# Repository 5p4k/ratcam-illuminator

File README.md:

Ratcam Illuminator
==================

**Official repository: [https://git.mittelab.org/proj/ratcam-illuminator](https://git.mittelab.org/proj/ratcam-illuminator)**

> Ratcam allows you to control your RaspberryPi camera through a Telegram bot, and alerts you when movement is detected, by sending photos and videos.

This project includes schematics for the IR illuminator board.

Please refer to the wiki page:
  - [Ratcam wiki (IT)](https://wiki.mittelab.org/progetti/5p4k/ratcam)
  - [Ratcam wiki (EN)](https://wiki.mittelab.org/en/progetti/5p4k/ratcam)

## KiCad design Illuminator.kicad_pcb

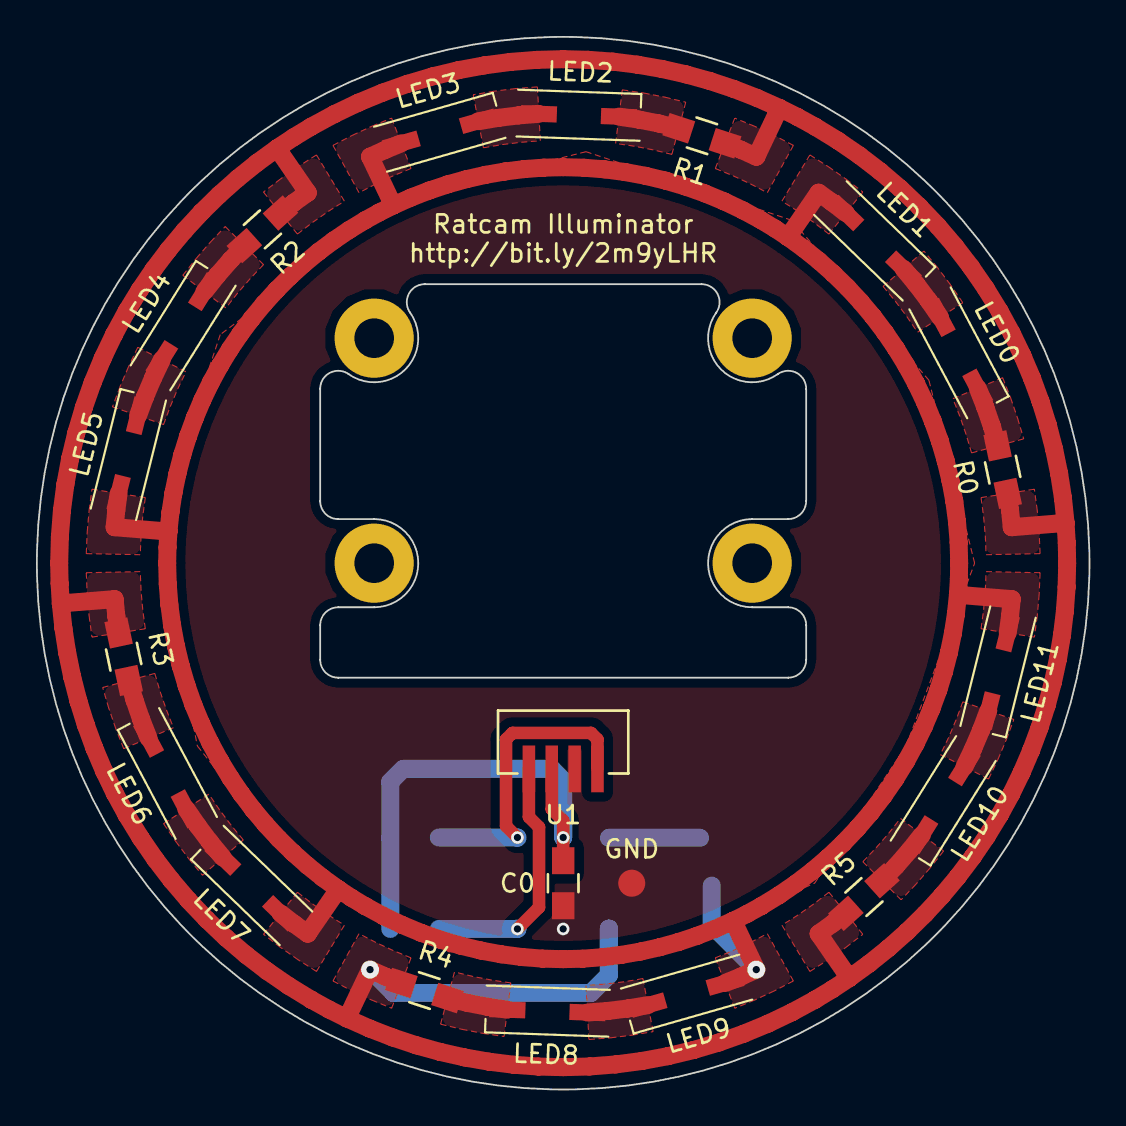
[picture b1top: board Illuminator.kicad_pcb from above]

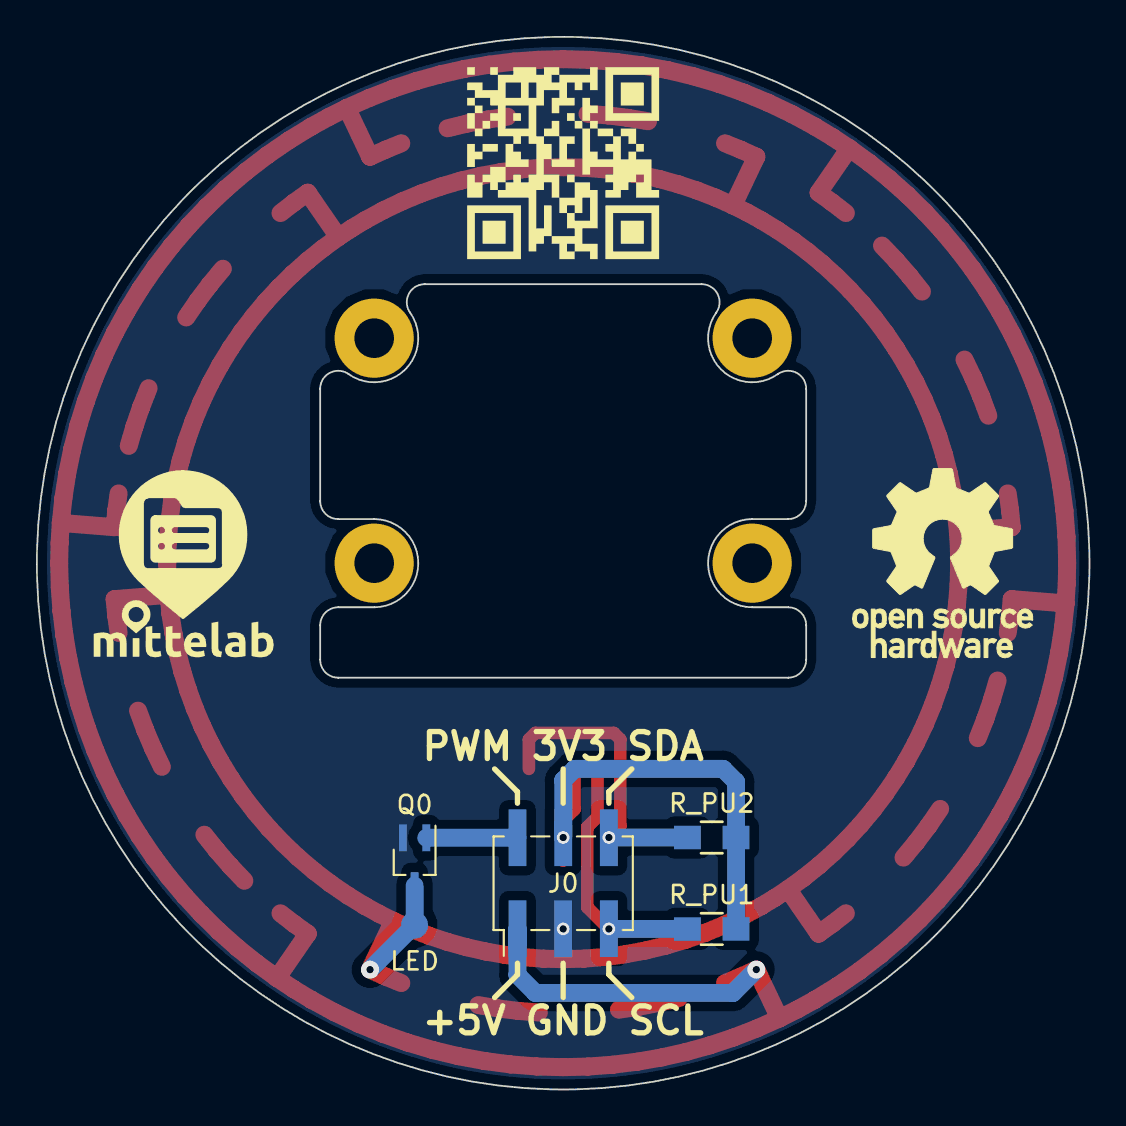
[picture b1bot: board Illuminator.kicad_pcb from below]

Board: 2 copper layers, 58.5 x 58.5 mm, 29 parts (8 on the bottom side), 19 nets.

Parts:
C0: 100nF; C_0805_HandSoldering
GND: Test_Point; Measurement_Point_Round-SMD-Pad_Small
J0: Conn_02x03_Top_Bottom; Pin_Header_Straight_2x03_Pitch2.54mm_SMD
LED: Test_Point; Measurement_Point_Round-SMD-Pad_Small
LED0, LED1, LED2, LED3, LED4, LED5, LED6, LED7, LED8, LED9, LED10, LED11: VSMY2850G; LED-GW_2.3x2.3mm_HandSoldering
Mittelab: Mittelab; MittelabLogo
OSHW: OpenSourceHardware; OSHWLogo
Q0: DMG1012UW; SOT-323_SC-70_Handsoldering
QRCode: Ratcam Illuminator; QRCode
R0, R1, R2, R3, R4, R5: 15; R_0805_HandSoldering
R_PU1, R_PU2: 4.7KΩ; R_0805_HandSoldering
U1: VEML7700

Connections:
+3V3: C0.1, J0.4, R_PU1.2, R_PU2.2, U1.2
+5V: J0.1, R0.1, R1.1, R2.1, R3.1, R4.1, R5.1
/TO_PWM: J0.2, Q0.1
/TO_SCL: J0.5, R_PU1.1, U1.1
/TO_SDA: J0.6, R_PU2.1, U1.4
GND: C0.2, GND.1, J0.3, Q0.2, U1.3
unnamed: LED0.1, LED1.2
unnamed: LED0.2, R0.2
unnamed: LED.1, LED1.1, LED3.1, LED5.1, LED7.1, LED9.1, LED11.1, Q0.3
unnamed: LED2.1, LED3.2
unnamed: LED2.2, R1.2
unnamed: LED4.1, LED5.2
unnamed: LED4.2, R2.2
unnamed: LED6.1, LED7.2
unnamed: LED6.2, R3.2
unnamed: LED8.1, LED9.2
unnamed: LED8.2, R4.2
unnamed: LED10.1, LED11.2
unnamed: LED10.2, R5.2

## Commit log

2017-10-13 Added nelist
2017-10-21 Adding LED 3D model to library
2017-10-21 Added original model files
2017-10-21 Resetting positions
2017-10-21 Mirroring resistor
2017-10-21 Adding round placement scripts
2017-10-21 Defaulting to a better position
2017-10-21 Orienting led properly
2017-10-21 Added arc track generator function
2017-10-21 Added circular tracks
2017-10-21 Changing names appropriately
2017-10-21 Restructuring Illuminator class.
    Added proper routing and settings.
2017-10-21 Giving a better name to the script
2017-10-22 Radial lines are orthogonal to the module
2017-10-22 Added overhang wire on the ring
2017-10-22 Applying the synthesizing script to the PCB
2017-10-22 Adding rotation offset to free space for mosfet
2017-10-22 Possible placement for mosfet
2017-10-22 Added copper fill around led pins
2017-10-22 Extra fill around radial tracks
2017-10-22 Added pin connector to schematics and net.
2017-10-22 Supporting placement and routing of connector and mosfet
2017-10-22 Adding back excess angle
2017-10-22 Merging the two script files into one
2017-10-22 Improving relative placement of pin and fet
2017-10-23 Routing with an horizontal segment to radius, easier placement for fet and pins
2017-10-23 Retouching angles
2017-10-23 Committing changes to PCB due to synthesize.py
2017-10-23 Filletting the big pads
2017-10-26 Rebooting dev
2017-10-26 Reading pcbnew data complete
2017-10-27 Pushing data back to kicad, added first placement test
2017-10-28 Bugfixes in radial.py and resetting pcb
2017-10-28 Rearranging options, fixing angle conversion and orienting resitors correctly
2017-10-28 Supporting vias, tracks and routing
2017-10-28 Bugfixes in routing
2017-10-28 Adding circular drawing for debug
2017-10-29 Fixing align_pads_to_chord method
2017-10-29 External rings addes
2017-10-29 Making pads equidistant
2017-10-29 Adding crown sector generation algorithm
2017-10-29 Adding fills, write only
2017-10-30 Added frontal copper pour, parallel to component axis or not
2017-10-30 Adding pour for nets that lead to ground and power too
2017-11-01 Re-arranging LEDs and selecting right components
2017-11-01 Added several features.
    Tracks and vias have width, Fills have fillet corner radius.
    Allowing for separators in the layout, effectively making all
    copper pours the same angular size.
2017-11-01 Resetting the layout from the new netlist
2017-11-01 Bugfix, int value required
2017-11-02 Added mosfet and connector position negotiation
2017-11-02 Fixing Flip
2017-11-03 Fixing placement
2017-11-05 Wrong default value in via.
2017-11-05 Routing connector and mosfet.
2017-11-07 Negotiating mosfet and connector position automatically.
2017-11-07 Fixing error in unit interval apx ratio
2017-11-07 Applying script
2017-11-07 Adding copper pours around the mosfet
2017-11-08 Added some text
2017-11-08 Using tighter radius.
    Added drawings and cuts for picamera
2017-11-08 Added GND 3V3 5V text
2017-11-08 Added QRcode
2017-11-08 Added correct edge cuts and outline DXF, plus QR code
2018-03-02 Added DS_Store
2018-03-02 Added library with VEML7700 footprint and schematic
2018-03-02 Ignoring other library specific files
2018-03-02 Added components and beginnning wiring of light sensor
2018-03-02 Converting symbols to non-legacy version. Wired up new ctk.
2018-03-02 Replaced all footprints with new ones, added links to materials
2018-03-02 Updated Netlist
2018-03-03 Added VEML7700 3d model
2018-03-04 Renamed and moved pieces
2018-03-04 Removed old wings file
2018-03-04 Fixing normals
2018-03-04 Exporting pieces as STL for the VEML7700
2018-03-04 Updating shape with correct normals and scale
2018-03-04 Adding wrl for VEML7700
2018-03-04 Again re-matching libraries to OSX Kicad's nightly
2018-03-04 Updating netlist due to previous change to footprints
2018-03-04 More missing footprints
2018-03-18 Updating to new layout with light sensor.
    Routing and placing mosfet and connector is now disable.
    Would not work in this case, also the layout is not so
    flexible that it can allow such routing.
    Added launcher script just to simplify invoking it
    from pcbnew.
2018-03-18 Added correctly rotated picamera layout with smaller margin.
2018-03-18 Routing and placing everything from scratch.
2018-03-18 Added models to R and C for rendering.
2018-03-18 Added QR code, Mittelab logo and OpenHardware logo
2018-03-18 Cleaning up schematics and remapping all elements in the PCB to the new netlist.
2018-03-18 Saved export settings
2018-06-27 First draft of case
2018-06-28 Added femal joint screw and lock
2018-06-28 Removed 0.1mm bezel which can't be 3dprinted
2018-07-11 Added illuminator goose neck
2018-07-13 First draft Raspberry Pi case
2018-07-19 Fixes at RPi case
2018-07-19 Completing joint and case
2018-07-25 Added STL files for case
2018-08-31 Including official repo url in readme
